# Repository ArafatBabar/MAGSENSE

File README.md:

# MagSense

<p align="center">

**An open-source multi-sensor magnetic field imaging platform.**

</p>

---

## Overview

MagSense is designed to measure the spatial distribution of magnetic fields rather than a single magnetic field value.

Instead of relying on one sensor, MagSense uses a synchronized array of five high-resolution magnetometers to capture magnetic field information at multiple locations simultaneously. This enables magnetic field visualization, gradient estimation and future magnetic source localization algorithms.

The project is being developed as an open-source hardware platform intended for research, education and experimentation.

---

# What's New in Rev.2

Rev.2 is a complete hardware redesign focused on improving signal integrity, reliability and manufacturability.

### Hardware Changes

- Migrated to STM32G431 with native USB support
- Redesigned 4-layer PCB architecture
- Added USB Type-C interface with ESD protection
- Implemented automatic power source selection
- Integrated CAN transceiver for future industrial communication
- Added Qwiic expansion connector
- Added onboard temperature sensor for future compensation
- Added RGB status indicator
- Improved debugging interface and test points
- Optimized routing for the magnetometer array

---

# Hardware

| Component | Device |
|------------|----------------|
| MCU | STM32G431CBT6 |
| Magnetometers | 5 × MMC5983MA |
| Temperature Sensor | TMP112 |
| USB | Native USB FS |
| Power MUX | TPS2115A |
| LDO | TPS7A0233 |
| CAN | TLT9251 |
| Expansion | Qwiic |

---

# Sensor Geometry

```
        Top

Left   Center   Right

      Bottom
```

Each outer sensor is positioned 20 mm from the center.

All sensors maintain identical orientation to simplify calibration and gradient calculations.

---

# Why Five Sensors?

Most low-cost magnetic sensing platforms use a single sensor and can only report the magnetic field at one location.

MagSense measures the magnetic field at five synchronized points, allowing future implementation of:

- Magnetic field interpolation
- Gradient estimation
- Vector field visualization
- Magnetic source localization
- Multi-point magnetic field analysis

---

# Repository

```
Hardware/
Firmware/
Software/
Documentation/
```

---

# Current Status

## Hardware

- [x] Architecture
- [x] Schematic
- [x] PCB Layout (Rev.2)
- [ ] PCB Fabrication
- [ ] Bring-up
- [ ] Validation

---

## Next Steps

- Prototype manufacturing
- Hardware validation
- Firmware development
- Sensor calibration
- Desktop visualization software

---

## License

Hardware: CERN-OHL-S v2

Firmware & Software: MIT

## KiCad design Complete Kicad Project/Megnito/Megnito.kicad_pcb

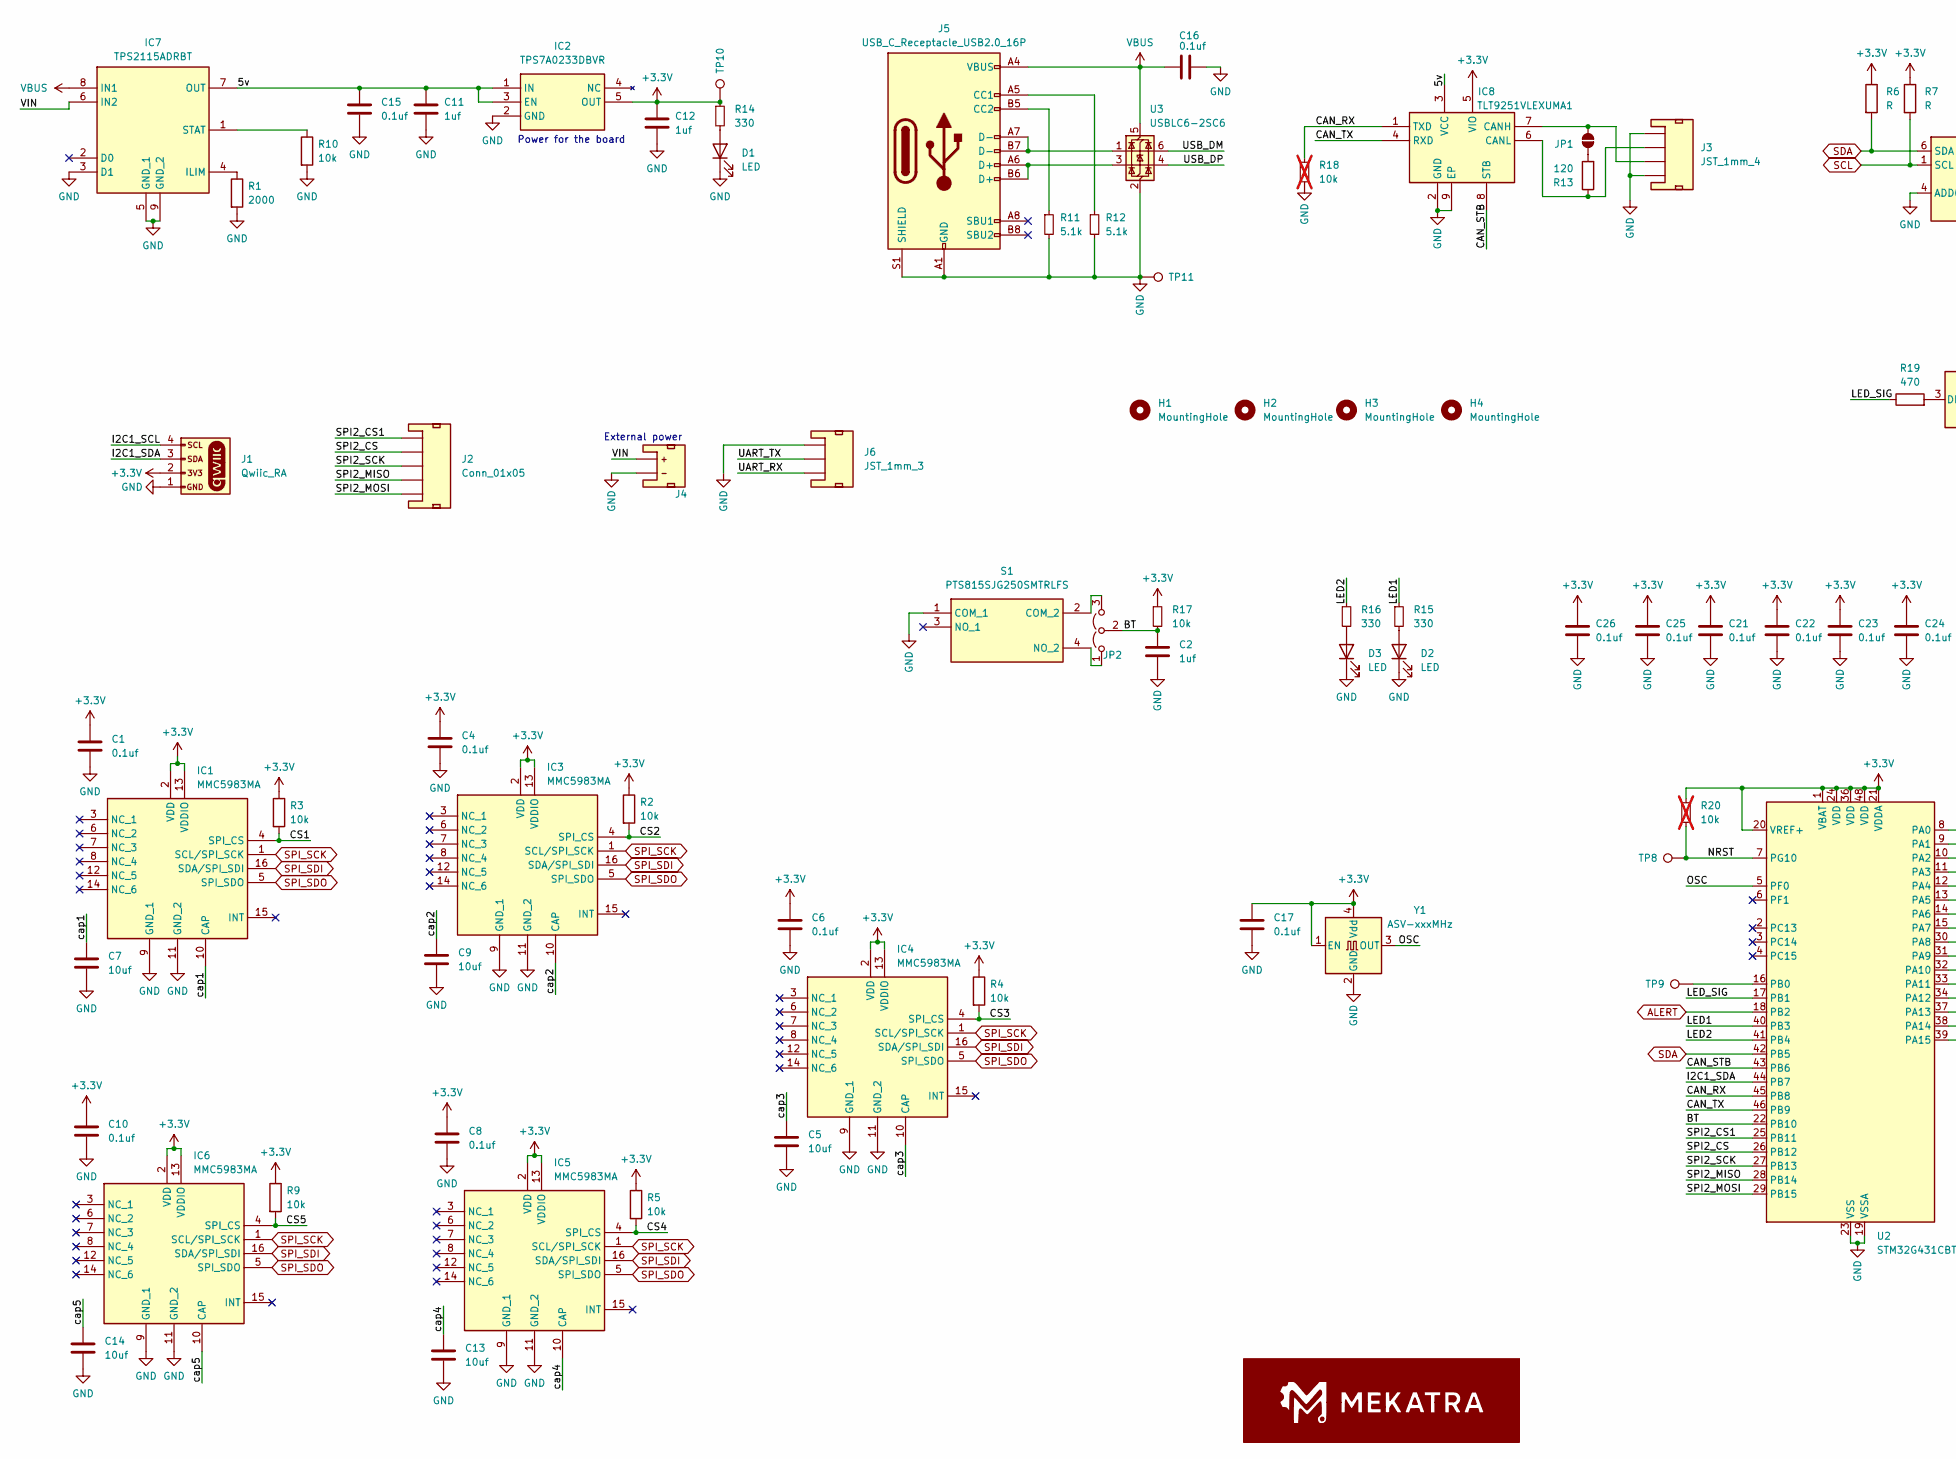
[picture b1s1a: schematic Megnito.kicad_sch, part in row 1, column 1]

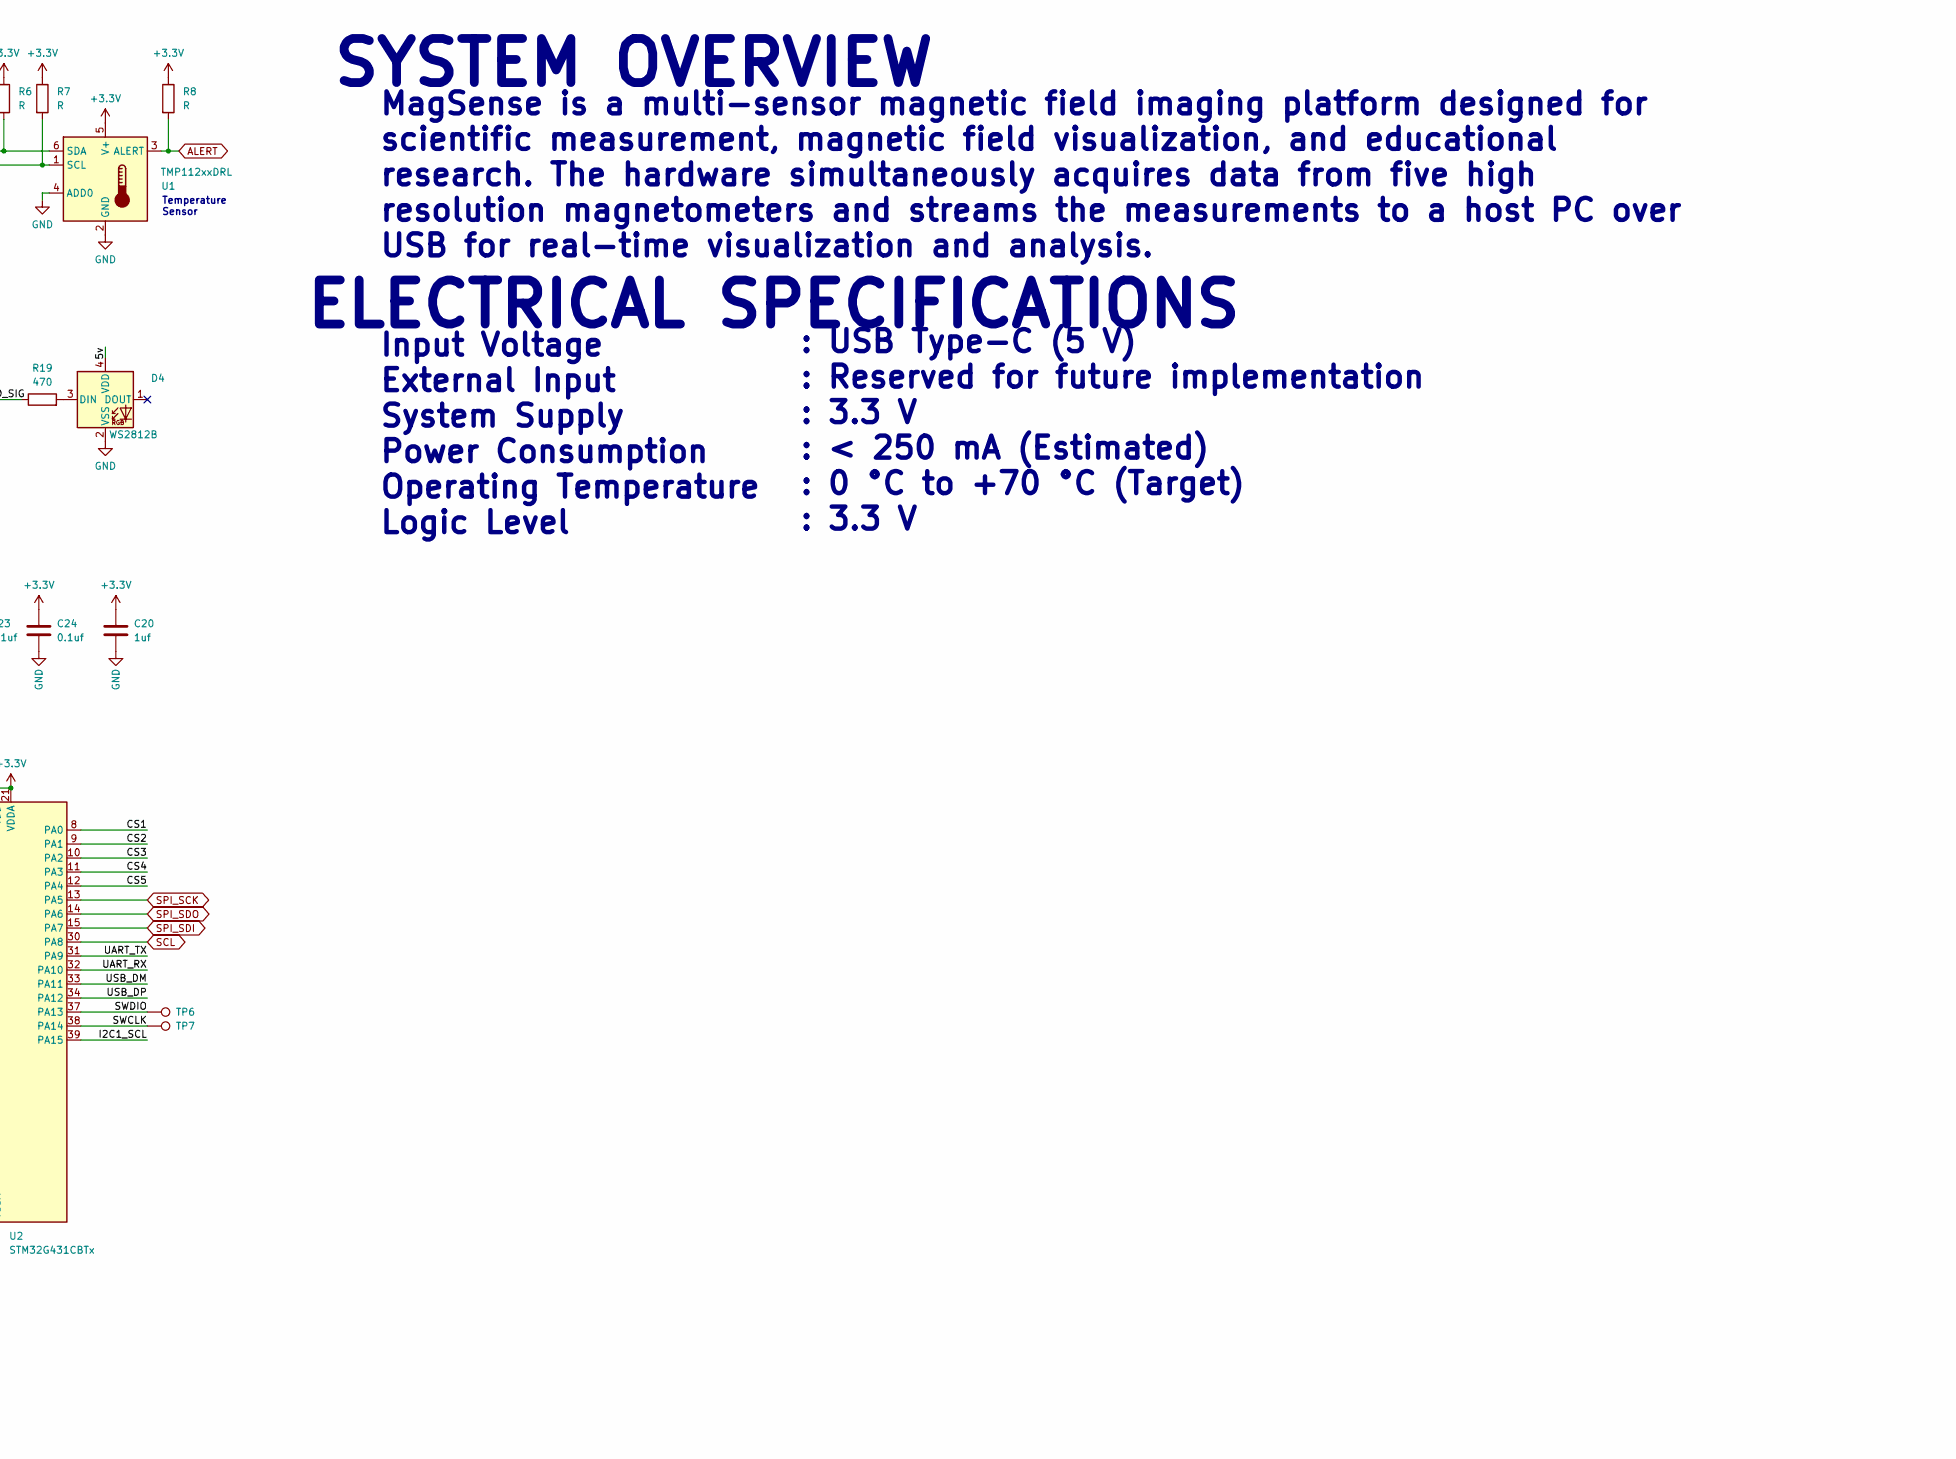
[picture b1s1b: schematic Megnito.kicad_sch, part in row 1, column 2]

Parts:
C1, C4, C6, C8, C10: 0.1uf; C_0603_1608Metric_Pad1.08x0.95mm_HandSolder
C2: 1uf; C_0603_1608Metric_Pad1.08x0.95mm_HandSolder
C5, C7, C9, C13, C14: 10uf; C_1206_3216Metric_Pad1.33x1.80mm_HandSolder
C11, C12, C20: 1uf; C_1210_3225Metric_Pad1.33x2.70mm_HandSolder
C15, C16, C17: 0.1uf; C_1210_3225Metric_Pad1.33x2.70mm_HandSolder
C21, C22, C23, C24, C25, C26: 0.1uf; C_0402_1005Metric_Pad0.74x0.62mm_HandSolder
D1, D2, D3: LED; LED_0402_1005Metric_Pad0.77x0.64mm_HandSolder
D4: WS2812B; LED_WS2812B-2020_PLCC4_2.0x2.0mm
H1, H2, H3, H4: MountingHole; MountingHole_2.2mm_M2_Pad_Via
IC1, IC3, IC4, IC5, IC6: MMC5983MA; Manufacturer_Part_Number MMC5983MA; Mouser Part Number 438-MMC5983MA
IC2: TPS7A0233DBVR; SOT95P280X145-5N; Manufacturer_Part_Number TPS7A0233DBVR; Mouser Part Number 595-TPS7A0233DBVR
IC7: TPS2115ADRBT; SON65P300X300X100-9N-D; Manufacturer_Part_Number TPS2115ADRBT; Mouser Part Number 595-TPS2115ADRBT
IC8: TLT9251VLEXUMA1; SON65P300X300X110-9N; Manufacturer_Part_Number TLT9251VLEXUMA1; Mouser Part Number 726-TLT9251VLEXUMA1
J1: Qwiic_RA; JST_1x04_P1.0mm_Horizontal_SMD
J2: Conn_01x05; JST_1x05_P1.0mm_Horizontal_SMD
J3: JST_1mm_4; JST_1x04_P1.0mm_Horizontal_SMD
J4: JST_2mm_LiPo; JST_1x02_P2.0mm_Horizontal_SMD
J5: USB_C_Receptacle_USB2.0_16P; USB_C_Receptacle_GCT_USB4085
J6: JST_1mm_3; JST_1x03_P1.0mm_Horizontal_SMD
JP1: Jumper_2_NO
JP2: Jumper_3_Open; Jumper_3_NO_NoSilk
R1: 2000; R_0402_1005Metric_Pad0.72x0.64mm_HandSolder
R2, R3, R4, R5, R9, R10, R17: 10k; R_0402_1005Metric_Pad0.72x0.64mm_HandSolder
R6, R7, R8: R; R_0603_1608Metric_Pad0.98x0.95mm_HandSolder
R11, R12: 5.1k; R_0402_1005Metric_Pad0.72x0.64mm_HandSolder
R13: 120; R_2512_6332Metric_Pad1.40x3.35mm_HandSolder
R14, R15, R16: 330; R_0402_1005Metric_Pad0.72x0.64mm_HandSolder
R18, R20: 10k; R_0402_1005Metric_Pad0.72x0.64mm_HandSolder; not fitted
R19: 470; R_0603_1608Metric_Pad0.98x0.95mm_HandSolder
S1: PTS815SJG250SMTRLFS; Manufacturer_Part_Number PTS815SJG250SMTRLFS
TP6: SWDIO; TestPoint_Pad_D1.0mm
TP7: SWCLK; TestPoint_Pad_D1.0mm
TP8: NRST; TestPoint_Pad_D1.0mm
TP9: PB0; TestPoint_Pad_D1.0mm
TP10: 3V3; TestPoint_Pad_D1.0mm
TP11: GND; TestPoint_Pad_D1.0mm
U1: TMP112xxDRL; SOT-563
U2: STM32G431CBTx; LQFP-48_7x7mm_P0.5mm
U3: USBLC6-2SC6; SOT-23-6
Y1: ASV-xxxMHz; Oscillator_SMD_Abracon_ASV-4Pin_7.0x5.1mm

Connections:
+3.3V: C1.1, C4.1, C6.1, C8.1, C10.1, C12.1, C17.1, C20.1, C21.1, C22.1, C23.1, C24.1, C25.1, C26.1, IC1.2 (VDD), IC1.13 (VDDIO), IC2.5 (OUT), IC3.2 (VDD), IC3.13 (VDDIO), IC4.2 (VDD), IC4.13 (VDDIO), IC5.2 (VDD), IC5.13 (VDDIO), IC6.2 (VDD), IC6.13 (VDDIO), IC8.5 (VIO), J1.2, R2.1, R3.1, R4.1, R5.1, R6.1, R7.1, R8.1, R9.1, R14.1, R17.1, R20.1, TP10.1, U1.5 (V+), U2.1 (VBAT), U2.20 (VREF+), U2.21 (VDDA), U2.24 (VDD), U2.36 (VDD), U2.48 (VDD), Y1.1 (EN), Y1.4 (Vdd)
/5v: C11.1, C15.1, D4.4 (VDD), IC2.1 (IN), IC2.3 (EN), IC7.7 (OUT), IC8.3 (VCC)
/BT: C2.1, JP2.2 (C), R17.2, U2.22 (PB10)
/CAN_RX: IC8.1 (TXD), R18.1, U2.45 (PB8)
/CAN_STB: IC8.8 (STB), U2.43 (PB6)
/CAN_TX: IC8.4 (RXD), U2.46 (PB9)
/CS1: IC1.4 (SPI_CS), R3.2, U2.8 (PA0)
/CS2: IC3.4 (SPI_CS), R2.2, U2.9 (PA1)
/CS3: IC4.4 (SPI_CS), R4.2, U2.10 (PA2)
/CS4: IC5.4 (SPI_CS), R5.2, U2.11 (PA3)
/CS5: IC6.4 (SPI_CS), R9.2, U2.12 (PA4)
/I2C1_SCL: J1.4, U2.39 (PA15)
/I2C1_SDA: J1.3, U2.44 (PB7)
/LED1: R15.1, U2.40 (PB3)
/LED2: R16.1, U2.41 (PB4)
/LED_SIG: R19.1, U2.17 (PB1)
/NRST: R20.2, TP8.1, U2.7 (PG10)
/OSC: U2.5 (PF0), Y1.3 (OUT)
/SPI2_CS: J2.2, U2.26 (PB12)
/SPI2_CS1: J2.1, U2.25 (PB11)
/SPI2_MISO: J2.4, U2.28 (PB14)
/SPI2_MOSI: J2.5, U2.29 (PB15)
/SPI2_SCK: J2.3, U2.27 (PB13)
/SWCLK: TP7.1, U2.38 (PA14)
/SWDIO: TP6.1, U2.37 (PA13)
/UART_RX: J6.3, U2.32 (PA10)
/UART_TX: J6.2, U2.31 (PA9)
/USB_DM: U2.33 (PA11), U3.6 (I/O1)
/USB_DP: U2.34 (PA12), U3.4 (I/O2)
/VIN: IC7.6 (IN2), J4.2 (+)
/cap1: C7.1, IC1.10 (CAP)
/cap2: C9.1, IC3.10 (CAP)
/cap3: C5.1, IC4.10 (CAP)
/cap4: C13.1, IC5.10 (CAP)
/cap5: C14.1, IC6.10 (CAP)
ALERT: R8.2, U1.3 (ALERT), U2.18 (PB2)
GND: C1.2, C2.2, C4.2, C5.2, C6.2, C7.2, C8.2, C9.2, C10.2, C11.2, C12.2, C13.2, C14.2, C15.2, C16.2, C17.2, C20.2, C21.2, C22.2, C23.2, C24.2, C25.2, C26.2, D1.1 (K), D2.1 (K), D3.1 (K), D4.2 (VSS), IC1.9 (GND_1), IC1.11 (GND_2), IC2.2 (GND), IC3.9 (GND_1), IC3.11 (GND_2), IC4.9 (GND_1), IC4.11 (GND_2), IC5.9 (GND_1), IC5.11 (GND_2), IC6.9 (GND_1), IC6.11 (GND_2), IC7.3 (D1), IC7.5 (GND_1), IC7.9 (GND_2), IC8.2 (GND), IC8.9 (EP), J1.1, J1.NC1 (NC), J1.NC2 (NC), J2.NC1, J2.NC2, J3.1, J3.4, J4.1 (-), J5.A1 (GND), J5.A12 (GND), J5.B1 (GND), J5.B12 (GND), J5.S1 (SHIELD), J6.1, J6.NC1, J6.NC2, R1.2, R10.2, R11.2, R12.2, R18.2, S1.1 (COM_1), TP11.1, U1.2 (GND), U1.4 (ADD0), U2.19 (VSSA), U2.23 (VSS), U2.35 (VSS), U2.47 (VSS), U3.2 (GND), Y1.2 (GND)
unnamed: D1.2 (A), R14.2
unnamed: D2.2 (A), R15.2
unnamed: D3.2 (A), R16.2
unnamed: D4.3 (DIN), R19.2
unnamed: IC7.4 (ILIM), R1.1
unnamed: IC7.1 (STAT), R10.1
unnamed: IC8.7 (CANH), J3.3, JP1.1 (A)
unnamed: IC8.6 (CANL), J3.2, R13.1
unnamed: J5.A5 (CC1), R12.1
unnamed: J5.B5 (CC2), R11.1
unnamed: J5.A6 (D+), J5.B6 (D+), U3.3 (I/O2)
unnamed: J5.A7 (D-), J5.B7 (D-), U3.1 (I/O1)
unnamed: JP1.2 (B), R13.2
unnamed: JP2.1 (A), S1.4 (NO_2)
unnamed: JP2.3 (B), S1.2 (COM_2)
unnamed: TP9.1, U2.16 (PB0)
SCL: R7.2, U1.1 (SCL), U2.30 (PA8)
SDA: R6.2, U1.6 (SDA), U2.42 (PB5)
SPI_SCK: IC1.1 (SCL/SPI_SCK), IC3.1 (SCL/SPI_SCK), IC4.1 (SCL/SPI_SCK), IC5.1 (SCL/SPI_SCK), IC6.1 (SCL/SPI_SCK), U2.13 (PA5)
SPI_SDI: IC1.16 (SDA/SPI_SDI), IC3.16 (SDA/SPI_SDI), IC4.16 (SDA/SPI_SDI), IC5.16 (SDA/SPI_SDI), IC6.16 (SDA/SPI_SDI), U2.15 (PA7)
SPI_SDO: IC1.5 (SPI_SDO), IC3.5 (SPI_SDO), IC4.5 (SPI_SDO), IC5.5 (SPI_SDO), IC6.5 (SPI_SDO), U2.14 (PA6)
VBUS: C16.1, IC7.8 (IN1), J5.A4 (VBUS), J5.A9 (VBUS), J5.B4 (VBUS), J5.B9 (VBUS), U3.5 (VBUS)

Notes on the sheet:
Power for the board
: USB Type-C (5 V) : Reserved for future implementation : 3.3 V : < 250 mA (Estimated) : 0 °C to +70 °C (Target) : 3.3 V
ELECTRICAL SPECIFICATIONS
SYSTEM OVERVIEW
MagSense is a multi-sensor magnetic field imaging platform designed for scientific measurement, magnetic field visualization, and educational research. The hardware simultaneously acquires data from five high resolution magnetometers and streams the measurements to a host PC over USB for real-time 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
Input Voltage External Input System Supply Power Consumption Operating Temperature Logic Level
External power
Temperature Sensor

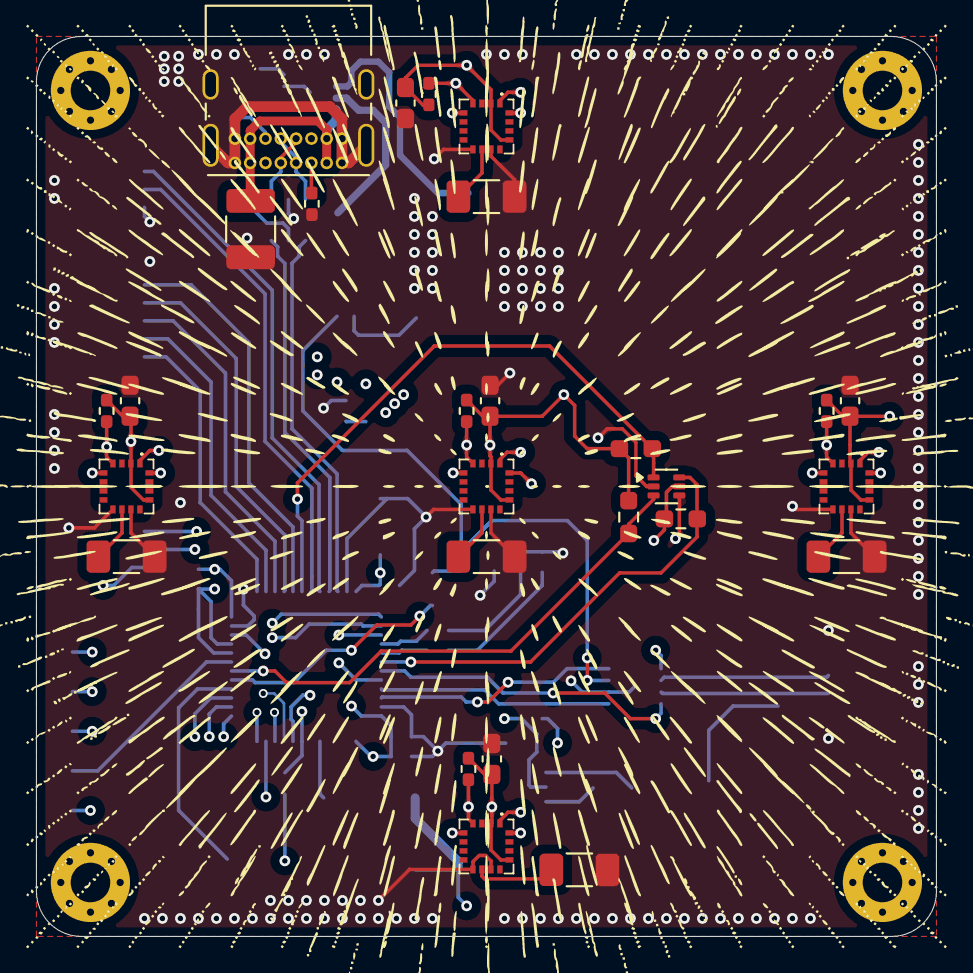
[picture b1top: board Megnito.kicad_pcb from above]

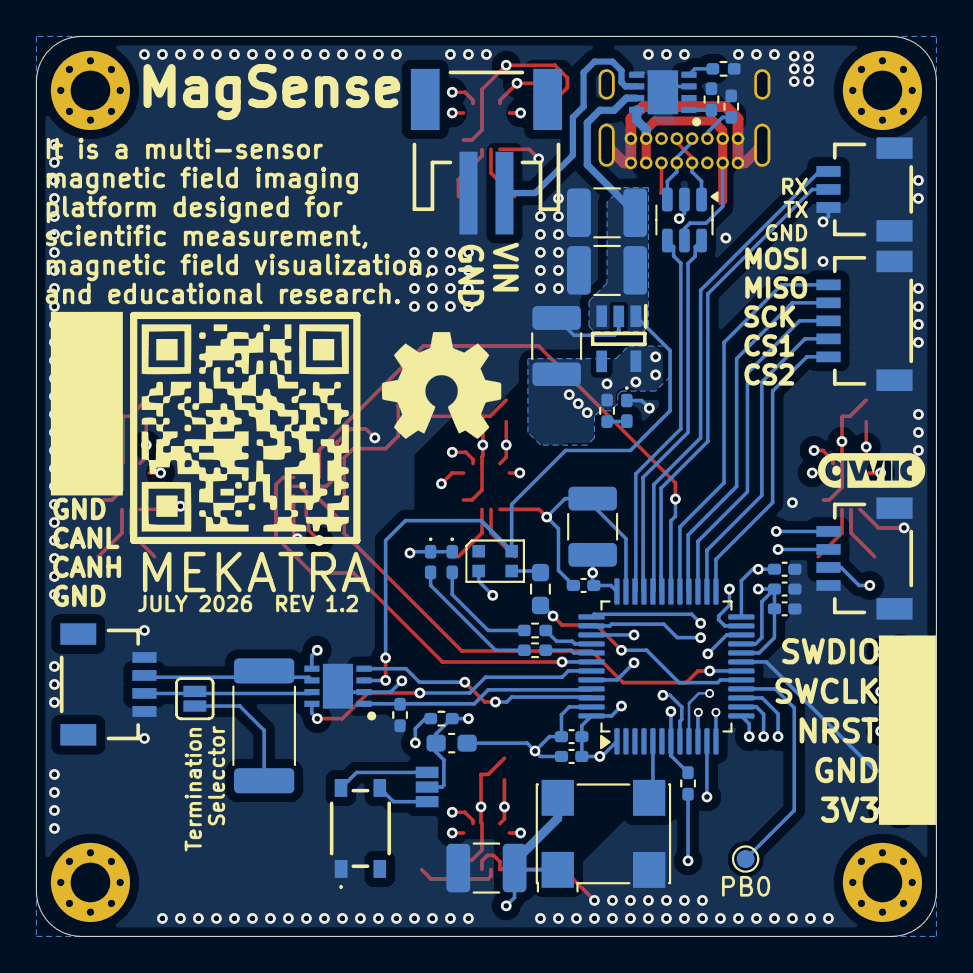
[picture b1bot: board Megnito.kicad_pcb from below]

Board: 6 copper layers, 50.0 x 50.0 mm, 78 parts (47 on the bottom side), 59 nets.
